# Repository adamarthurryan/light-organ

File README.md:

light-organ
===========

The light organ is an audio visualizer or special effects controller. The device is an electronic a 3-channel dimmer for incandescent lights. Each channel interprets the amplitude of one frequency band from the input audio.

This device was used in the interactive sound ard installation "infinite space kaleidoscope" by Adam Brown. See http://madanworb.com/blog/2011/02/01/infinite-space-kaleidoscope/

# Hardware

The dimmer is implemented with TRIAC switches, signaled through optoisolators. The dimmer controller and sound analyzer is implemented with an Atmel ATXMega128A1 8-bit microcontroller. 

The dimmer circuitry also provides a rectified AC-sync signal at 2.5V. The controller analyzes this signal to determine when the TRIAC should be switched on at each point in the AC waveform. (Recall that TRIACs can only be switched off at zero-crossing, so dimmer PWM has to be syncronized to the AC carrier wave.)

Circuits were designed in the free edition of Eagle. Schematics and burnable board layouts are included in the "circuits/light organ base" and "circuits/light organ controller" folders.

# Software

The controller software is implemented for the Atmel ATXMega128A1 - an 8-bit, 32MHz microcontroller. The responsibilities of the controller software are to:
- analyze an input waveform to find amplitudes in the three target frequency bands
- analyze the AC-sync signal to determine the mains frequency and phase
- signal the amplitude for each channel by switching the TRIACs

The software is developed and compiled with Atmel AVR Studio and depends on the XMega appnote library.

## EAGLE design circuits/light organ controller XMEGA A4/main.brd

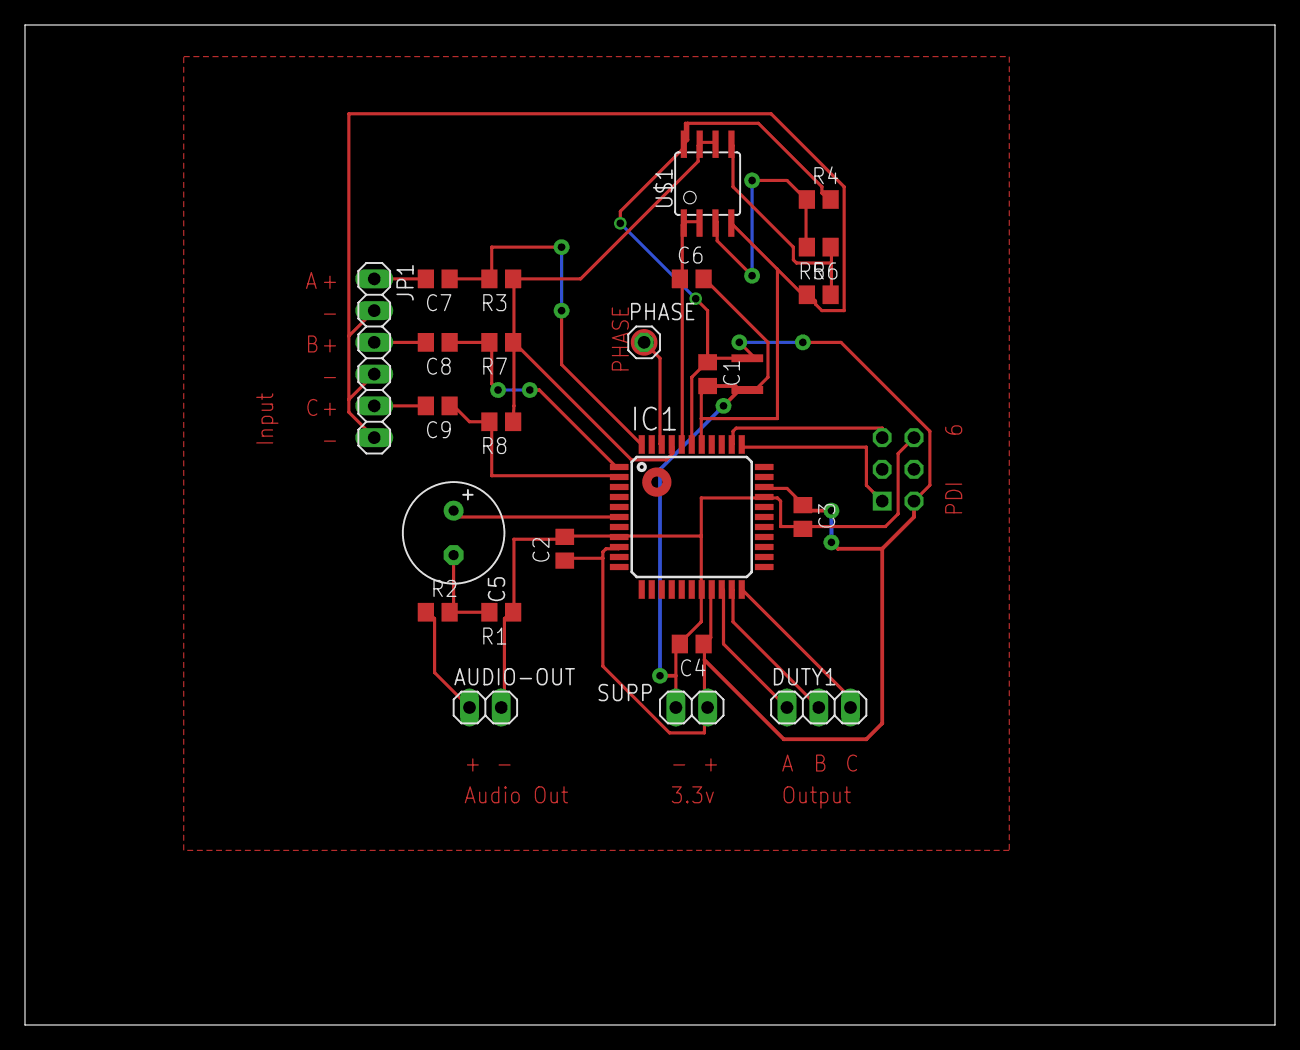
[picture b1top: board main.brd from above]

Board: 2 copper layers, 100.0 x 80.0 mm, 27 parts (1 on the bottom side), 23 nets.

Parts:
AUDIO-OUT: 1X02
C1, C2, C3, C4: C0805
C5: 100u; E3,5-8
C6: 0.1u; C0805
C7, C8, C9: 2.2u; C0805
DUTY1: 1X03
IC1: AVR_XMEGA_A4_44A; TQFP44
JP1: 1X06
PHASE: 1X01
PROG: AVR-ISP-6
R1, R3, R7, R8: 20k; R0805
R2: 1k; R0805
R4, R5, R6: 10k; R0805
SUPP: 1X02
U$1: MCP6002SMT; SOIC8
U$2, U$4: RESISTOR-0; JOINED-PADS

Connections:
+3V3: C2.1, C3.1, C4.1, IC1.9, IC1.19, IC1.31, PROG.2, SUPP.1, U$2.P$1
AGND: C1.2, IC1.38, JP1.2, JP1.4, JP1.6, R6.1, U$1.4, U$4.P$2
AREF: C6.1, IC1.40, U$1.1, U$1.2
AREF/2: IC1.41, R3.1, R7.1, R8.1, U$1.6, U$1.7
AVCC: C1.1, IC1.39, R4.2, U$1.8, U$2.P$2
GND: AUDIO-OUT.2, C2.2, C3.2, C4.2, C6.2, IC1.8, IC1.18, IC1.30, PROG.6, R1.1, SUPP.2, U$4.P$1
IN1: C7.2, JP1.1
unnamed: IC1.35, PROG.5
unnamed: C5.+, IC1.6
unnamed: IC1.34, PROG.1
unnamed: C5.-, R1.2, R2.2
unnamed: AUDIO-OUT.1, R2.1
unnamed: C7.1, IC1.44, R3.2
unnamed: IC1.42, PHASE.1
unnamed: C8.2, JP1.3
unnamed: R4.1, R5.2, U$1.3
unnamed: R5.1, R6.2, U$1.5
unnamed: C9.2, JP1.5
unnamed: C8.1, IC1.1, R7.2
unnamed: C9.1, IC1.2, R8.2
unnamed: DUTY1.1, IC1.20
unnamed: DUTY1.2, IC1.21
unnamed: DUTY1.3, IC1.22

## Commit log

2014-11-25 D D initial checkin of project files
